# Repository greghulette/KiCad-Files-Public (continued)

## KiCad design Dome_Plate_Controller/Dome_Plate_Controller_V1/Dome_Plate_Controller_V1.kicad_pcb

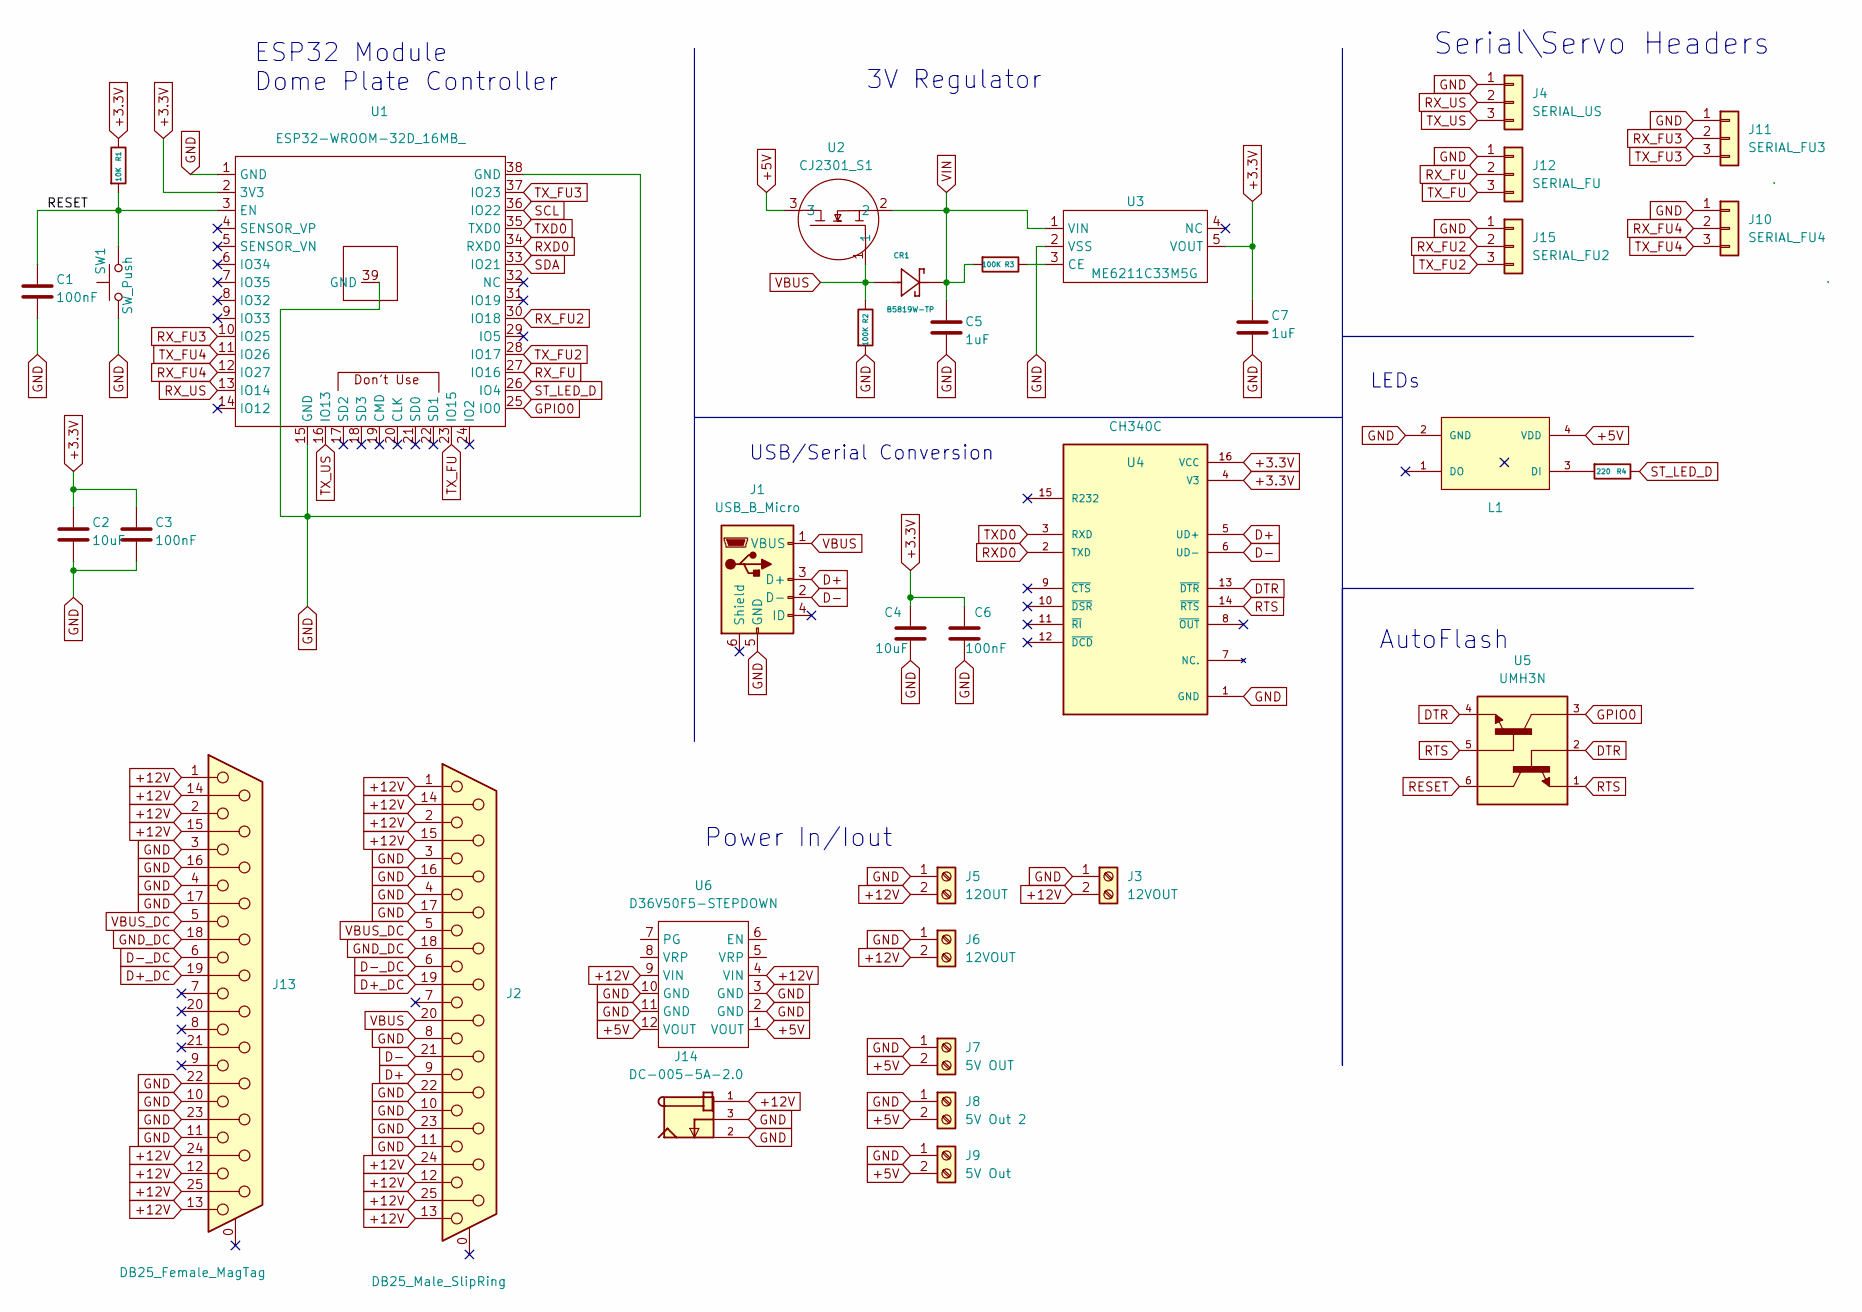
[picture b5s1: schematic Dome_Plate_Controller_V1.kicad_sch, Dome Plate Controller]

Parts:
C1, C3, C6: 100nF; C_0402_1005Metric; LCSC C307331
C2, C4: 10uF; C_0402_1005Metric; LCSC C315248
C5, C7: 1uF; C_0402_1005Metric; LCSC C77009
CR1: B5819W-TP; SOD3716X135N; LCSC C84354
J1: USB_B_Micro; USB_Micro-B_Amphenol_10118194_Horizontal; LCSC C132563
J2: DB25_Male_SlipRing; DSUB-25_Male_Vertical_P2.77x2.84mm_MountingHoles; LCSC C2984302
J3, J6: 12VOUT; TerminalBlock_4Ucon_1x02_P3.50mm_Horizontal; LCSC C474892
J4: SERIAL_US; Molex_KK-254_AE-6410-03A_1x03_P2.54mm_Vertical; LCSC C471416
J5: 12OUT; TerminalBlock_4Ucon_1x02_P3.50mm_Horizontal; LCSC C474892
J7: 5V OUT; TerminalBlock_4Ucon_1x02_P3.50mm_Horizontal; LCSC C474892
J8: 5V Out 2; TerminalBlock_4Ucon_1x02_P3.50mm_Horizontal; LCSC C474892
J9: 5V Out; TerminalBlock_4Ucon_1x02_P3.50mm_Horizontal; LCSC C474892
J10: SERIAL_FU4; Molex_KK-254_AE-6410-03A_1x03_P2.54mm_Vertical; LCSC C471416
J11: SERIAL_FU3; Molex_KK-254_AE-6410-03A_1x03_P2.54mm_Vertical; LCSC C471416
J12: SERIAL_FU; Molex_KK-254_AE-6410-03A_1x03_P2.54mm_Vertical; LCSC C471416
J13: DB25_Female_MagTag; DSUB-25_Female_Vertical_P2.77x2.84mm_MountingHoles; LCSC C2938621
J14: DC-005-5A-2.0; XKB_DC-005-5A-2.0; PARTREV A0; LCSC C3010535
J15: SERIAL_FU2; Molex_KK-254_AE-6410-03A_1x03_P2.54mm_Vertical; LCSC C471416
L1: WS2812B-2020; LCSC C965555
R1: 10K; R_0603_1608Metric; LCSC C269701
R2, R3: 100K; R_0603_1608Metric; LCSC C25803
R4: 220; R_0402_1005Metric; LCSC C25091
SW1: SW_Push; TS-1101S-B-B-B-W-A; LCSC C692465
U1: ESP32-WROOM-32D_16MB_; ESP32-WROOM-32; LCSC C529578
U2: CJ2301_S1; SOT-23; LCSC C8547
U3: ME6211C33M5G; SOT-23-5; LCSC C82942
U4: CH340C; SOIC127P600X180-16N; PARTREV 2G; LCSC C84681
U5: UMH3N; UMT6; LCSC C62892
U6: D36V50F5-STEPDOWN

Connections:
+3.3V: C2.1, C3.1, C4.1, C6.1, C7.1, R1.1, U1.2 (3V3), U3.5 (VOUT), U4.4 (V3), U4.16 (VCC)
+5V: J7.2, J8.2, J9.2, L1.4 (VDD), U2.3, U6.1 (VOUT), U6.12 (VOUT)
+12V: J2.1, J2.2, J2.12, J2.13, J2.14, J2.15, J2.24, J2.25, J3.2, J5.2, J6.2, J13.1, J13.2, J13.12, J13.13, J13.14, J13.15, J13.24, J13.25, J14.1, U6.4 (VIN), U6.9 (VIN)
D+: J1.3 (D+), J2.9, U4.5 (UD+)
D+_DC: J2.19, J13.19
D-: J1.2 (D-), J2.21, U4.6 (UD-)
D-_DC: J2.6, J13.6
DTR: U4.13 (~DTR), U5.2, U5.4
GND: C1.2, C2.2, C3.2, C4.2, C5.1, C6.2, C7.2, J1.5 (GND), J2.3, J2.4, J2.8, J2.10, J2.11, J2.16, J2.17, J2.22, J2.23, J3.1, J4.1, J5.1, J6.1, J7.1, J8.1, J9.1, J10.1, J11.1, J12.1, J13.3, J13.4, J13.10, J13.11, J13.16, J13.17, J13.22, J13.23, J14.2, J14.3, J15.1, L1.2 (VSS), R2.2, SW1.1, U1.1 (GND), U1.15 (GND), U1.38 (GND), U1.39 (GND), U3.2 (VSS), U4.1 (GND), U6.2 (GND), U6.3 (GND), U6.10 (GND), U6.11 (GND)
GND_DC: J2.18, J13.18
GPIO0: U1.25 (IO0), U5.3
unnamed: L1.3 (DI), R4.2
unnamed: R3.1, U3.3 (CE)
RESET: C1.1, R1.2, SW1.2, U1.3 (EN), U5.6
RTS: U4.14 (~RTS), U5.1, U5.5
RXD0: U1.34 (RXD0), U4.2 (TXD)
RX_FU: J12.2, U1.27 (IO16)
RX_FU2: J15.2, U1.30 (IO18)
RX_FU3: J11.2, U1.10 (IO25)
RX_FU4: J10.2, U1.12 (IO27)
RX_US: J4.2, U1.13 (IO14)
SCL: U1.36 (IO22)
SDA: U1.33 (IO21)
ST_LED_D: R4.1, U1.26 (IO4)
TXD0: U1.35 (TXD0), U4.3 (RXD)
TX_FU: J12.3, U1.23 (IO15)
TX_FU2: J15.3, U1.28 (IO17)
TX_FU3: J11.3, U1.37 (IO23)
TX_FU4: J10.3, U1.11 (IO26)
TX_US: J4.3, U1.16 (IO13)
VBUS: CR1.A, J1.1 (VBUS), J2.20, R2.1, U2.1
VBUS_DC: J2.5, J13.5
VIN: C5.2, CR1.C, R3.2, U2.2, U3.1 (VIN)

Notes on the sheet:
ESP32 Module Dome Plate Controller
3V Regulator
LEDs
Power In/Iout
USB/Serial Conversion
AutoFlash
Serial\Servo Headers

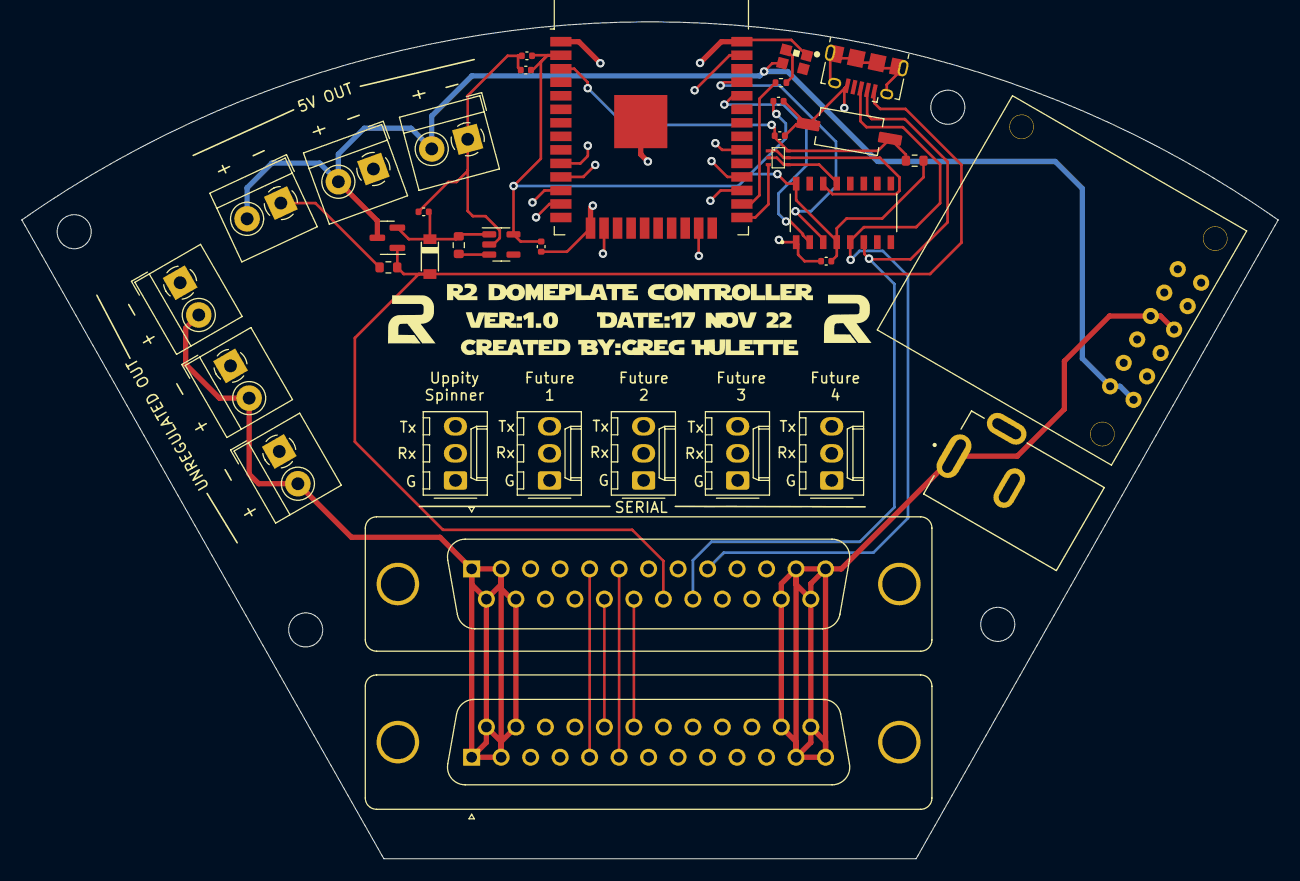
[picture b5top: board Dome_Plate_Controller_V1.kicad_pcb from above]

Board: 4 copper layers, 118.0 x 78.6 mm, 35 parts (0 on the bottom side), 31 nets.

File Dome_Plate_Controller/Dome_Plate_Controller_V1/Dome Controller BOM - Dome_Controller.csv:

Comment,Designator,Cmp name,Footprint,LCSC part number
100nF,"C1, C3, C6, ",C,Capacitor_SMD:C_0402_1005Metric,C307331
10uF,"C2, C4, ",C,Capacitor_SMD:C_0402_1005Metric,C315248
1uF,"C5, C7, ",C,Capacitor_SMD:C_0402_1005Metric,C77009
B5819W-TP,"CR1, ",B5819W-TP_1,Custom:SOD3716X135N,C84354
WS2812B-2020,"J1, ",USB_B_Micro,Connector_USB:USB_Micro-B_Amphenol_10118194_Horizontal,C965555
USB_B_Micro,"J2, ",Conn_01x06,Connector_PinHeader_2.54mm:PinHeader_1x06_P2.54mm_Vertical,C132563
Header Male 2.54_1x06,"J3, ",Conn_02x03_Odd_Even,Connector_PinHeader_2.54mm:PinHeader_2x03_P2.54mm_Vertical,C37208
Header-Male_02x03_Odd_Even,"J4, J10, ",Conn_01x03,Connector_PinHeader_2.54mm:PinHeader_1x03_P2.54mm_Vertical,C49257
Header-Male-_01x03,"J5, ",Screw_Terminal_01x02,TerminalBlock_4Ucon:TerminalBlock_4Ucon_1x02_P3.50mm_Horizontal,C49257
2 pin Screw Terminal 3.5mm,"J6, ",Screw_Terminal_01x02,TerminalBlock_4Ucon:TerminalBlock_4Ucon_1x02_P3.50mm_Horizontal,C474892
2 pin Screw Terminal 3.5mm,"J7, ",Screw_Terminal_01x02,TerminalBlock_4Ucon:TerminalBlock_4Ucon_1x02_P3.50mm_Horizontal,C474892
2 pin Screw Terminal 3.5mm,"J8, ",Screw_Terminal_01x02,TerminalBlock_4Ucon:TerminalBlock_4Ucon_1x02_P3.50mm_Horizontal,C474892
2 pin Screw Terminal 3.5mm,"J9, ",Screw_Terminal_01x02,TerminalBlock_4Ucon:TerminalBlock_4Ucon_1x02_P3.50mm_Horizontal,C474892
2 pin Screw Terminal 3.5mm,"L1, ",WS2812B-2020,Custom:WS2812B-2020,C474892
10K,"R1, ",R,Resistor_SMD:R_0603_1608Metric,C190321
100K,"R2, R3, ",R,Resistor_SMD:R_0603_1608Metric,C25741
TS-1101S-B-B-B-W-A,"SW1, ",SW_Push,Custom:TS-1101S-B-B-B-W-A,C692465
ESP32-WROOM-32D_16MB_,"U1, ",ESP32-WROOM-32-Custom,RF_Module:ESP32-WROOM-32,C473012
CJ2301_S1,"U2, ",CJ2301_S1,Package_TO_SOT_SMD:SOT-23,C8547
ME6211C33M5G,"U3, ",ME6211C33M5G,Package_TO_SOT_SMD:SOT-23-5,C82942
CH340C,"U4, ",CH340C,Custom:SOIC127P600X180-16N,C84681
UMH3N,"U5, ",UMH3N,Custom:UMT6,C62892
